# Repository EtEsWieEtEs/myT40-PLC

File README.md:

# myT40-PLC  (SPS) based on Teensy 4.0 (Version-5)
Hardware for PLC based on Teensy 4.0, covering all my needs. I have to replace my 30 years old PS4-141-MM1 from "Klöcker Moeller", reusing the original case of this model PS4-141-MM1.

Picture: Prototype V3

Motivation for a “Mighty 40”
----------------------------
Since the late 1990s, I have been working with four used PS4-141s, one PS4-341, both controllers from Klöckner Moeller, and about two dozen 24V AC surge relays (unfortunately not DC), commonly known as “Eltako,” I planned and developed my “smart home” in the late ’90s and installed it in my new house in 2002. 
The bus systems for building automation that were already on the market at the time were out of the question for me due to licensing issues and costs. 
These control units are networked and seamlessly integrated into my sub-distribution panels—commonly known as “fuse boxes”—on a circuit breaker (C) rail installed at the rear, just like standard circuit breakers. Circuit protection, power, and control are clearly separated in accordance with VDE standards.

Using serial communication, the master controller can be configured during operation using a user-friendly VB program (timer functions, lighting, roller shutters, light level detection, assignment of switches to power outlets such as wall sockets or ceiling outlets for lamps, etc.).

Since these controllers or similar devices are no longer manufactured in this format, the first failures occurred after nearly 30 years of trouble-free operation, and no other manufacturer offers affordable controllers with galvanic isolation(!) in this format anymore, I decided to strip down the PS4-141 housings and develop a new circuit that handles the most important functions and fits into these very housings I have on hand, hereinafter referred to as the “original housing.”

The result is "myT40-PLC", a combination of extention slot of PS4-341 in the housing of an P4S-141.

It is not intended to create a replica of the original, nor is that the goal. Externally, the case has been noticeably modified and fitted with different connectors: the “myT40-PLC”.

Since the circuit itself might also be of interest to others, I designed the main board in two versions for J3: one with an FFC connector, the “FFC” version, for my personal replacement in the original case, and a standard version with a pin header, the “PFS” version, to inspire replicas in any case. The latter is presented here.

This pin header connector "PFS" version offers a 2x DAC option and a 2x ADC option, while allowing the use of all 32 digital I/O channels and providing Sub-D connectors for bus systems in a separate housing. This distinguishes it from the FFC version, which cannot optionally provide all outputs when the DAC and ADC are installed and connected.

A parallel project, myT41-Controller, focuses on a controller unit that provides a graphical interface, Ethernet, CAN and RS485 buses, as well as a serial OTA interface, and allows the myT40 PLC to be controlled, logged, and configured.
With appropriate programming, the myT41C controller can also be used as a protocol converter or logger on the interfaces for entirely different projects.

The software will be documented separately at a later date.
This document describes only the hardware-related port definitions that result from the circuit and are essential for programming.

Attended documents describe the "Final Version V5" as "V3.3 M44", based on experience of 4 prototypes build up in the past 5 years.

The current Version is the final one waiting to be build-up: V5.
I made a lot of changes and enhancements and transfered these features as well to the myT41-Controller.

myT40-PLC      Requirements for my new PLC
------------------------------------------
Even though the new circuit cannot meet all the requirements of the original, I still have a clear idea of what it will be capable of.
The new controller should

1. be installed in my existing original enclosures or any other enclosures,
2. be networked so it can communicate with other devices,
3. ensure isolated potentials for inputs, load circuits, bus systems, ADC/DAC, and controllers; therefore, commercially available Arduino- or Raspberry Pi-based PLCs are out of the question,
4. provide 16 digital inputs and 16 digital outputs as needed, with isolated potentials,
5. support interrupts for input bytes,
6. Provide 4 analog-to-digital converter inputs if required, two of these are fed via built-in setpoint potentiometers,
7. Provide 2 digital-to-analog converter outputs if required,
8. Process analog signals from 0..10V, ADC and DAC, with their own reference potential,
9. Support up to two CAN buses, galvanically isolated, optionally GND, PE shield via capacitor,
10. Provide an RS485 interface for 16 clients, galvanically isolated, bus termination with low-drop diodes or optionally classically with switchable terminating resistor 720/120/720 ,
11. RS485 connection corresponds to the original (V5); the DIN sockets combine CAN1/2 and RS485,
12. be based on a modern, fast processor with sufficient RAM,
13. be supported by an EEPROM/Flash memory,
14. have ICs mounted on sockets wherever possible,
15. support a mode selector switch with 3 modes, including a setting for a cold start via RESET,
16. be able to use the existing RESET button,
17. be able to trigger a RESET via software, including a choice between cold or warm start,
18. ensure local communication via SPI for the interface and function modules,
19. be energy-efficient and operate at 3.3V,
20. be programmed in C or C++,
21. allow communication with a PC or a control unit via CAN, RS485, Ethernet,
22. enable flexible programming,
23. feature a pluggable, wired 3.6V backup lithium battery with its own ADC monitoring,
24. Respond to the 24V AC “Eltako” devices present in the building’s electrical system with 5ms DC pulses (!),
25. Monitor the supply voltages of the CPU and the direct interfaces and, if necessary, perform a warm start or cold start with a reset,     
26. Control the onboard hardware watchdog and/or software watchdog in combination with the operating mode switch, or allow them to function independently.
27. Does not support flexible docking of various original expansion modules; however, a suitable connection panel for SPI and digital I/O is available, though it is incompatible with original expansion modules. Instead, equip the existing 16-channel digital output unit with a new “header board” to make	it usable.
28. No online programming or programming via network, although this might actually be possible.
29. No PWM support on the outputs or counter features on the inputs.
30. External hardware watchdog with adjustable times, including a definable delay on RESET and restart (V5),
31. Buttons for Teensy 4.0 boot/program and on/off (V5),
32. OTA option (V5).
33. F-RAM SPI Option based on SOIC-8

Current developement
---------------------

Picture: Prototype V4 below, original defective pcb at top

Now that the Prototype 4 (V4) is working successfully with a 4-layer PCB, I have added an external watchdog and a delay into Version 5.

V5 offers optionally the use of OTA via one of the two serial interfaces instead of a second CAN bus.

Furthermore I think F-RAM is a good alternative for often changed written data to be stored permantly. So V5 provides a place for SOIC-8 alterntive to EEPROM in DIL-8.

However, Version 5 has not yet been built or tested. That is planned for the coming months.

There are some things to do like translation of documentation into English or Spanish, perhaps in next winter.
The current documentation is in German. 
So please be pacient, feel free and be inspired.

Licence
---------------------
This work is licensed under the Creatjve Commons Atuributjon-NonCommercial-ShareAlike 4.0 Internatjonal
License. To view a copy of this license, visit htup://creatjvecommons.org/licenses/by-nc-sa/4.0/ or send a
letuer to Creatjve Commons, PO Box 1866, Mountain View, CA 94042, USA.
This license lets others remix, adapt, and build upon your work non-commercially, as long as they credit you
and license their new creatjons under the identjcal terms.
htup://creatjvecommons.org/licenses/by-nc-sa/4.0/

  Title    myT40-PLC Documentation

  Author   Clemens Niesen, Germany, 2026

  Source   These documents

  Licence  CC-BY-NC-SA

DISCLAIMER
----------

I explicitly state that I make no representations or warranties regarding non-infringement or the absence of other defects with respect to the CC-licensed work.This means that users use the work at their own risk.

Furthermore, I point out that this project and the content of this documentation, as well as associated files, is purely a recreational project and should be understood as a case study for the reader. 

This project, these circuits are not tested or approved by official bodies. Errors can not be excluded despite all care. Whoever reproduces this project does so at his own risk and responsibility. I do not take any responsibility for damages to persons and devices, material, buildings, animals, etc..

Rebuilding is reserved exclusively for experienced people who know exactly what they are doing.  What third-party use of the control with third does and does not, lies apart from the craftsmanship of the construction also with the software, which is also beyond my responsibility. I give no guarantee and take no responsibility for the content of references, links and quotes.

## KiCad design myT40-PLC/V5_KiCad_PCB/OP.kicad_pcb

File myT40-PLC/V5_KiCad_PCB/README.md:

KiCad 9.0.7

myT40-PLC Rev3.3 M44 V5 PFS

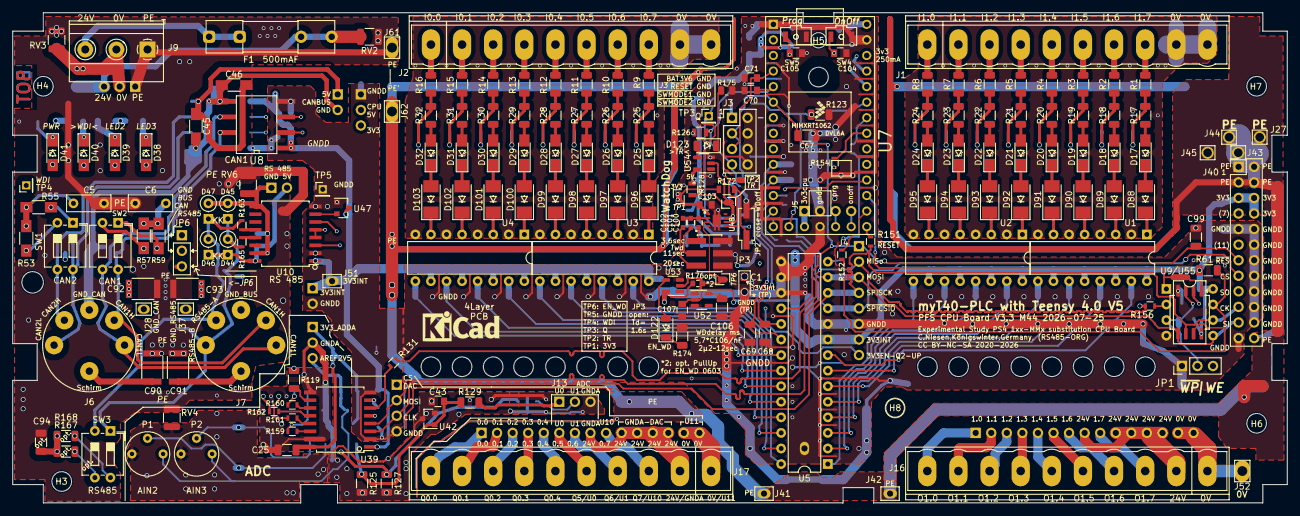
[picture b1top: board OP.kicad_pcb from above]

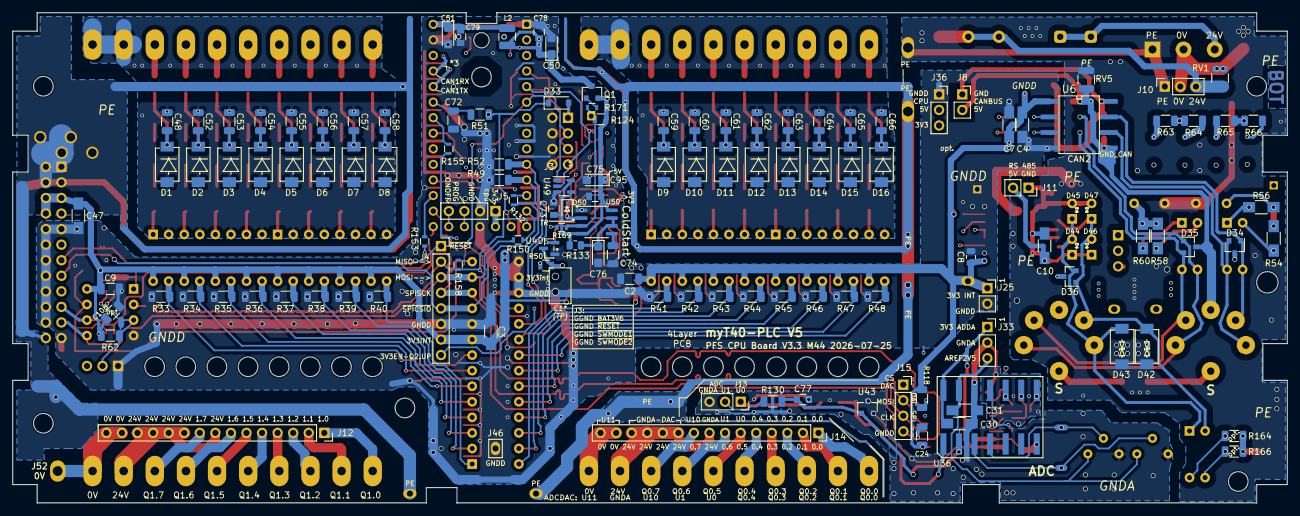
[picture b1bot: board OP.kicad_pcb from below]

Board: 4 copper layers, 208.0 x 80.0 mm, 341 parts (127 on the bottom side), 234 nets.

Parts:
A2: KiCad-Symbol; KiCad-Logo_5mm_SilkScreen
C1: Siehe Text; CP_EIA-3216-18_Kemet-A
C2, C9, C24, C25, C48, C52, C53, C54, C55, C56, C57, C58, C59, C60, C61, C62, C63, C64, C65, C66, C67, C68, C69, C72, C99, C108: 100n; C_1206_3216Metric
C3, C4, C7, C10, C30, C31, C47: 100n; C_1206_HandSoldering
C5, C6: 4n7; C_Rect_L7.0mm_W2.5mm_P5.00mm
C8: 100n; C_0805_2012Metric
C43, C77: 100p; C_0805
C45, C46: 100n 100V; C_1206_HandSoldering
C50, C51: 4µ7 16V; CP_EIA-3216-18_Kemet-A
C70, C71, C73, C75, C103, C104, C105, C107: 100n; C_0805
C74: 10n; C_1206_3216Metric
C76, C95: 10µ 10V; CP_EIA-3216-18_Kemet-A
C78, C79: 2,2pF; C_0805
C90, C91, C92, C93: 220n 250V; C_1812
C94: 220p 50V; C_1206_3216Metric
C100: 47n; C_0603
C101: 150n; C_0603
C102: 270n; C_0603
C106: 2µ2; C_1206_3216Metric
D1, D2, D3, D4, D5, D6, D7, D8, D9, D10, D11, D12, D13, D14, D15, D16: P6SMB 5,0CA SMD; DO-214AA_man
D17, D18, D19, D20, D21, D22, D23, D24, D25, D26, D27, D28, D29, D30, D31, D32, D38, D39, D40, D41: APTD3216; LED_1206_HandSoldering
D33: 1N4448W7F DII; D_SOD-123
D34, D35, D36: SZNUP2105LT1G; SOT-23
D42, D43: P6SMB 5,0CA; DO-214AA_man
D44, D45, D46, D47: BAT 46; D_DO-35_SOD27_P2.54mm_Vertical_KathodeUp
D50: RB751V40T1G; D_SOD-323
D88, D89, D90, D91, D92, D93, D94, D95, D96, D97, D98, D99, D100, D101, D102, D103: 1N4448W7F DII; Diode_DO213AB-MELF_SOD123
D122, D123: APTD3216; LED_1206_3216_big-gap
F1: 500mA F; Fuseholder_Clip-5x20mm_Littelfuse_111_Inline_P20.00x5.00mm_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
H1: MH2,5; Hole_2,5mm
H2: MH3,5; Hole_3,5mm
H3, H4, H5, H6, H7, H8: MountingHole; MountingHole_3.2mm_M3
H9, H10, H11, H12, H13, H14, H15, H16, H17, H18, H19, H20, H21, H22, H23, H24: LED3.2mm; Hole_3.2mm
J1, J2, J16, J17: MSTBVA-2.5-10-5.08; TerminalBlock_Phoenix_MSTBVA-2.5-10-5.08_1x10_P5.08mm_Horiz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
J3: 02x04; PinHeader_2x04_P2.54mm_Vertical
J4: 01x08_fem; PinSocket_1x08_P2.54mm_Vertical
J5, J15: 01x04_fem; PinSocket_1x04_P2.54mm_Vertical
J6, J7: DIN-5; DIN-5-180
J8, J11, J25: 01x02_fem; PinSocket_1x02_P2.54mm_Vertical
J9: Ub 0V PE; TerminalBlock_Phoenix_MKDS-1,5-3-5.08_1x03_P5.08mm_Horizont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
J10, J13, J33, J36: 01x03_fem; PinSocket_1x03_P2.54mm_Vertical
J12, J14: 01x15_fem; PinSocket_1x15_P2.54mm_Vertical
J27, J44, J45: Lötauge; Lötauge-Junction-2x2-1.4
J28: GND_CAN; Lötauge-Junction-2x1.5
J37: Lötauge; Lötauge-Junction-2x1.5
J40: Extention; PinHeader_2x12_P2.54mm_Vertical
J41, J42, J46, J51: Lötauge; Lötauge-Junction
J43: Flachstecker; Lötauge-Junction-2x2-1.4
J52: Lötauge; Lötauge-Junction-3.5x2.5-1.6
J61, J62: Lötauge; Lötauge-Junction-3.5x2.0-1.6
JP1: WP_; PinHeader_1x03_P2.54mm_Vertical
JP2: Jumper_NC_Small; PinHeader_2x01_P2.54mm_Vertical_SMD
JP3: jumper field; SAMTEC_TMMH-103-01-G-DV-A_PinHeader-02x03-SMD
JP6: GND-DEF.J7; PinHeader_1x03_P2.54mm_Vertical
L2: 47µH; L_1210_3225Metric
P1, P2: 1,0K lin; Trimmer_Vishay_T7YA
Q1: IRLML 2244; SOT-23
R1, R2, R3, R4, R5, R6, R7, R8, R9, R10, R11, R12, R13, R14, R15, R16: 6k8 500mW; R_1206_3216Metric
R17, R18, R19, R20, R21, R22, R23, R24, R25, R26, R27, R28, R29, R30, R31, R32: 1k1; R_1206_3216Metric
R33, R34, R35, R36, R37, R38, R39, R40, R41, R42, R43, R44, R45, R46, R47, R48: 3k3; R_1206_3216Metric
R49, R52, R61, R62, R118, R119: 10k; R_1206_3216Metric
R50, R126: 220; R_0805
R51, R123: 680k; R_1206_3216Metric
R53, R54, R55, R56, R57, R58, R59, R60: 120; R_1206_HandSoldering
R63, R64, R65, R66, R174: 1650; R_1206_3216Metric
R124: 10k; R_0805
R125, R127: 30k 0,1%; R_1206_3216Metric
R128: 47k; R_0805
R129, R130: 90k 0,1%; R_1206_3216Metric
R131, R132, R150, R151, R152, R153, R154, R155, R156, R158, R159, R160, R161, R162: 51; R_0603
R133: 220k; R_0805_2012Metric
R163, R165, R169, R171: 10; R_0603
R164, R166, R167, R168: 120; R_1206_3216Metric
R172: 1k; R_1206_vertical
R175: 3k3; R_0805_2012Metric
R176: 10k; R_0603_1608Metric
RV1, RV2, RV3: 31VDC; R_1210_3225Metric
RV4, RV5, RV6: 46VAC; R_1210_3225Metric
SW1, SW2: SW_DIP_x02; SW_DIP_SPSTx02_Slide_6.7x6.64mm_W7.62mm_P2.54mm_LowProfile
SW3: GDS0204; SW_DIP_SPSTx02_Slide_6.7x6.64mm_W7.62mm_P2.54mm_LowProfile
SW4: OnOff; switch-tactil_OMRON_B3U-3000P
SW5: Prog; switch-tactil_OMRON_B3U-3000P
TP1: 3V3; TestPoint_SMD
TP2: TR; TestPoint_SMD
TP3: Q; PinHeader_1x01_P2.00mm_Vertical
TP4: WDI; PinHeader_1x01_P2.00mm_Vertical
TP5: GNDD; PinHeader_1x01_P2.00mm_Vertical
TP6: EN_WD; TestPoint_SMD
U1, U2, U3, U4: LTV-844; DIP-16_W7.62mm_cut
U5: MCP23S17; DIP-28_W7.62mm
U6, U8: ISO1050; SOP-8
U7: Teensy4.0; Teensy40wo34_0.9
U9: 25LC512; DIP-8_W7.62mm
U10: ADM2483xRW; SOIC-16W_7.5x10.3mm_Pitch1.27mm_handsoldered
U36: MCP3204; DIL-14-SMD
U39: ADuM1401xRW; SOIC-16W_7.5x10.3mm_Pitch1.27mm_handsoldered
U40: ADM-803S; SOT-23
U42, U43: LM4040 AIM3-2.5; SOT-23
U47: ADM-809Z; SOT-23
U48: TPS3431; VSON-8_EP_2.8x2.8_Pitch0.65mm
U49: SN74LV1T32; SOT-23-5
U50: NE555DRG4; SOIC-8_3.9x4.9mm_P1.27mm
U52: S-80929CNMC; SOT-23-5
U53, U54: BD7LS04G-C; SOT-23-5
U55: FM25V10; SOIC-8_5.3x6.2mm_P1.27mm

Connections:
3V3: C103.1, J36.3, R50.1, R126.2, R172.1, R176.1, TP1.1, U40.3 (VCC), U48.1 (VDD), U53.5 (3V3)
5V_CPU: C73.2, C75.2, C95.1, J36.2, Q1.2 (S), R124.2, R128.2, R133.2, U49.5 (5V_CPU), U50.4 (R), U50.8 (VCC), U54.5 (5V_CPU)
/3V3EN_Q2_UP: J4.8, R169.2
/3V3_ADDA: C25.2, C30.2, J33.1, R119.2, U36.14 (Vdd), U39.16 (VDD2)
/3V3_CPU: J5.1, U7.16 (3V3)
/3V3_INT: C1.1, C2.1, C3.2, C4.1, C7.2, C8.1, C9.2, C24.2, C47.2, C107.1, C108.2, D41.2 (A), J4.7, J25.1, J40.5, J40.6, J40.8, J51.1, R61.1, R62.1, R118.2, U1.10, U1.12, U1.14, U1.16, U2.10, U2.12, U2.14, U2.16, U3.10, U3.12, U3.14, U3.16, U4.10, U4.12, U4.14, U4.16, U5.9 (VDD), U6.1 (VCC1), U8.1 (VCC1), U9.8 (VCC), U10.1 (VDD1), U39.1 (VDD1), U47.3 (VCC), U52.2 (VDD), U55.8 (VCC)
/5V_CPU_final: C51.1, C79.1, L2.2, U7.33 (VIN)
/AIN0: J13.1, R129.1
/AIN1: J13.2, R130.1
/AREF_2V5: C31.2, J33.3, P1.3, P2.3, U36.13 (Vref)
/BAT3V6: D33.2 (A), J3.1
/BAT_CHECK: C72.1, R51.2, U7.28 (21_A7_RX5_BCLK1)
/CAN1H: D35.2 (A2), J6.5, J7.5, SW2.4, U8.7 (CANH)
/CAN1L: D35.1 (A1), J6.3, J7.3, SW2.3, U8.6 (CANL)
/CAN1RX: U7.30 (23_A9_CRX1_MCLK1), U8.2 (RXD)
/CAN1TX: U7.29 (22_A8_CTX1), U8.3 (TXD)
/CAN2H: D34.1 (A1), J6.4, SW1.3, U6.7 (CANH)
/CAN2L: D34.2 (A2), J6.1, SW1.4, U6.6 (CANL)
/CAN2RX: U6.2 (RXD), U7.2 (0_RX1_CRX2)
/CAN2TX: U6.3 (TXD), U7.3 (1_TX1_CTX2)
/CH0: C43.1, R125.1, R129.2, U36.1 (CH0), U42.1 (K)
/CH1: C77.1, R127.1, R130.2, U36.2 (CH1), U43.1 (K)
/CH2: P1.2, U36.3 (CH2)
/CH3: P2.2, U36.4 (CH3)
/CLK: R159.2, U36.11 (CLK)
/Din: R161.2, U36.9 (Din)
/Dout: R160.2, U36.10 (Dout)
/EN_WD: R176.2, TP6.1, U48.3 (EN), U52.1 (OUT), U53.2
/GND_CAN_BUS: C45.2, C46.1, C92.1, D34.3 (common), D35.3 (common), J6.2, J8.2, J28.1, JP6.1 (A), RV5.2, U6.5 (GND2), U8.5 (GND2)
/GND_RS485_BUS: C10.1, C93.2, D36.3 (common), D45.2 (A), D47.2 (A), J11.1, J37.1, JP6.3 (B), RV6.2, U10.9 (GND2), U10.15 (GND2)
/INTA: C69.1, R52.1, U5.20 (INTA), U7.10 (8_TX2_IN1)
/INTB: C68.1, R49.1, U5.19 (INTB), U7.11 (9_OUT1C)
/I_GPA0: R48.2, U4.9, U5.21 (GPA0)
/I_GPA1: R47.2, U4.11, U5.22 (GPA1)
/I_GPA2: R46.2, U4.13, U5.23 (GPA2)
/I_GPA3: R45.2, U4.15, U5.24 (GPA3)
/I_GPA4: R44.2, U3.9, U5.25 (GPA4)
/I_GPA5: R43.2, U3.11, U5.26 (GPA5)
/I_GPA6: R42.2, U3.13, U5.27 (GPA6)
/I_GPA7: R41.2, U3.15, U5.28 (GPA7)
/I_GPB0: R40.2, U2.9, U5.1 (GPB0)
/I_GPB1: R39.2, U2.11, U5.2 (GPB1)
/I_GPB2: R38.2, U2.13, U5.3 (GPB2)
/I_GPB3: R37.2, U2.15, U5.4 (GPB3)
/I_GPB4: R36.2, U1.9, U5.5 (GPB4)
/I_GPB5: R35.2, U1.11, U5.6 (GPB5)
/I_GPB6: R34.2, U1.13, U5.7 (GPB6)
/I_GPB7: R33.2, U1.15, U5.8 (GPB7)
/LED1: D40.2 (A), TP4.1, U7.7 (5_IN2), U48.6 (WDI)
/LED2: D39.2 (A), U7.8 (6_OUT1D)
/LED3: D38.2 (A), U7.9 (7_RX2_OUT1A)
/MISO: J4.2, J40.17, R131.1, R156.2, R158.2, U7.14 (12_MISO_MQSL)
/MISO_0: R156.1, U9.2 (MISO), U55.2 (MISO)
/MOSI: J4.3, J15.2, J40.21, R150.1, U5.13 (SI), U9.5 (MOSI), U39.4 (VIB), U55.5 (MOSI)
/ONOFF: C104.1, J5.4, SW4.2, U7.19 (ON_OFF)
/PROGRAM: C105.1, J5.3, SW5.2, U7.18 (PROGRAM)
/Q: R124.1, R169.1, R171.1, TP3.1, U50.3 (Q)
/RS485_A: D36.1 (A1), D42.2 (A2), D46.2 (A), D47.1 (K), J7.4, R163.1, SW3.2
/RS485_B: D36.2 (A2), D43.2 (A2), D44.2 (A), D45.1 (K), J7.1, R165.1, SW3.1
/SPISCK: J4.4, J15.3, J40.19, R151.1, U5.12 (SCK), U9.6 (SCK), U39.3 (VIA), U55.6 (SCK)
/TR-U50: D50.2 (A), R128.1, TP2.1, U40.2 (~RESET), U48.7 (~WDO), U50.2 (TR), U54.2
/U0V: J9.2, J10.2, RV1.1, RV3.2
/U24V: F1.2, J10.3, RV1.2, RV2.2
/UART_RX: U7.23 (16_A2_RX4_SCL1), U10.3 (RxD)
/UART_TX: U7.24 (17_A3_TX4_SDA1), U10.6 (TxD)
/Ub_5V_RS485_BUS: C10.2, D44.1 (K), D46.1 (K), J11.2, U10.16 (VDD2)
/Ub_CAN_BUS: C45.1, C46.2, J8.1, U6.8 (VCC2), U8.8 (VCC2)
/VBAT: D33.1 (K), R51.1, R123.1, U7.15 (VBAT)
/~CS: R162.2, U36.8 (~CS/SHDN)
/~EE_HOLD: R61.2, R152.1, U9.7 (~HOLD), U55.7 (~HOLD)
/~RESET: C67.1, C99.2, J3.3, J4.1, J40.13, R50.2, U5.18 (~RESET), U7.6 (4_BCLK2), U49.1
/~SPICS_ADC: R154.1, U39.5 (VIC)
/~SPICS_DAC: J15.1, R155.1
/~SPICS_EE: R153.1, U9.1 (~CS), U55.1 (~CS)
/~SPICS_IO: J4.5, J40.15, R132.1, U5.11 (~CS)
/~SW_MODE_1: C71.1, J3.5, U7.4 (2_OUT2)
/~SW_MODE_2: C70.1, J3.7, R126.1, U7.5 (3_LRCLK2), U49.2
/~UART_RE: U7.25 (18_A4_SDA0), U10.4 (~RE), U10.5 (DE)
/~WP: JP1.2 (C), R62.2, U9.3 (~WP), U55.3 (~WP)
GNDA: C25.1, C30.1, C31.1, C43.2, C77.2, J13.3, J33.2, P1.1, P2.1, R125.2, R127.2, RV4.2, U36.7 (DGND), U36.12 (AGND), U39.9 (GND2), U39.15 (GND2), U42.2 (A), U42.3 (3(A)), U43.2 (A), U43.3 (3(A))
GNDD: C1.2, C2.2, C3.1, C4.2, C7.1, C8.2, C9.1, C24.1, C47.1, C50.2, C51.2, C67.2, C68.2, C69.2, C70.2, C71.2, C72.2, C73.1, C74.1, C75.1, C76.2, C78.2, C79.2, C95.2, C99.1, C103.2, C104.2, C105.2, C106.2, C107.2, C108.1, J3.2, J3.4, J3.6, J3.8, J4.6, J5.2, J15.4, J25.2, J36.1, J40.9, J40.10, J40.12, J40.14, J40.16, J40.18, J40.20, J40.22, J40.23, J46.1, JP1.1 (A), JP2.2, JP3.02, JP3.04, JP3.06, R33.1, R34.1, R35.1, R36.1, R37.1, R38.1, R39.1, R40.1, R41.1, R42.1, R43.1, R44.1, R45.1, R46.1, R47.1, R48.1, R49.2, R52.2, R63.1, R64.1, R65.1, R66.1, R123.2, R174.1, R175.1, SW4.1, SW5.1, TP5.1, U5.10 (VSS), U5.15 (A0), U5.16 (A1), U5.17 (A2), U6.4 (GND1), U7.1 (GND), U7.17 (GND), U7.32 (GND), U8.4 (GND1), U9.4 (GND), U10.2 (GND1), U10.8 (GND1), U39.2 (GND1), U39.8 (GND1), U40.1 (GND), U47.1 (GND), U48.4 (GND), U48.9 (Pad), U49.3 (GNDD), U50.1 (GND), U52.3 (VSS), U53.3 (GNDD), U54.3 (GNDD), U55.4 (GND)
unnamed: C5.2, R53.1, R54.1, R55.1, R56.1
unnamed: C6.2, R57.1, R58.1, R59.1, R60.1
unnamed: C90.2, J6.S
unnamed: C91.2, J7.S
unnamed: C94.2, R164.2, R166.2, R167.2, R168.2
unnamed: C100.2, JP3.01
unnamed: C101.1, JP3.03
unnamed: C102.1, JP3.05
unnamed: C48.1, C52.1, C53.1, C54.1, C55.1, C56.1, C57.1, C58.1, D1.1 (A1), D2.1 (A1), D3.1 (A1), D4.1 (A1), D5.1 (A1), D6.1 (A1), D7.1 (A1), D8.1 (A1), J1.9, J1.10, U1.2, U1.4, U1.6, U1.8, U2.2, U2.4, U2.6, U2.8
unnamed: C48.2, D1.2 (A2), R1.1, R17.2
unnamed: C52.2, D2.2 (A2), R2.1, R18.2
unnamed: C53.2, D3.2 (A2), R3.1, R19.2
unnamed: C54.2, D4.2 (A2), R4.1, R20.2
unnamed: C55.2, D5.2 (A2), R5.1, R21.2
unnamed: C56.2, D6.2 (A2), R6.1, R22.2
unnamed: C57.2, D7.2 (A2), R7.1, R23.2
unnamed: C58.2, D8.2 (A2), R8.1, R24.2
unnamed: C59.2, D9.2 (A2), R9.1, R25.2
unnamed: C59.1, C60.1, C61.1, C62.1, C63.1, C64.1, C65.1, C66.1, D9.1 (A1), D10.1 (A1), D11.1 (A1), D12.1 (A1), D13.1 (A1), D14.1 (A1), D15.1 (A1), D16.1 (A1), J2.9, J2.10, U3.2, U3.4, U3.6, U3.8, U4.2, U4.4, U4.6, U4.8
unnamed: C60.2, D10.2 (A2), R10.1, R26.2
unnamed: C61.2, D11.2 (A2), R11.1, R27.2
unnamed: C62.2, D12.2 (A2), R12.1, R28.2
unnamed: C63.2, D13.2 (A2), R13.1, R29.2
unnamed: C64.2, D14.2 (A2), R14.1, R30.2
unnamed: C65.2, D15.2 (A2), R15.1, R31.2
unnamed: C66.2, D16.2 (A2), R16.1, R32.2
unnamed: D17.2 (A), R17.1
unnamed: D17.1 (K), D88.2 (A)
unnamed: D18.2 (A), R18.1
unnamed: D18.1 (K), D89.2 (A)
unnamed: D19.2 (A), R19.1
unnamed: D19.1 (K), D90.2 (A)
unnamed: D20.2 (A), R20.1
unnamed: D20.1 (K), D91.2 (A)
unnamed: D21.2 (A), R21.1
unnamed: D21.1 (K), D92.2 (A)
unnamed: D22.2 (A), R22.1
unnamed: D22.1 (K), D93.2 (A)
unnamed: D23.2 (A), R23.1
unnamed: D23.1 (K), D94.2 (A)
unnamed: D24.2 (A), R24.1
unnamed: D24.1 (K), D95.2 (A)
unnamed: D25.2 (A), R25.1
unnamed: D25.1 (K), D96.2 (A)
unnamed: D26.2 (A), R26.1
unnamed: D26.1 (K), D97.2 (A)
unnamed: D27.2 (A), R27.1
unnamed: D27.1 (K), D98.2 (A)
unnamed: D28.2 (A), R28.1
unnamed: D28.1 (K), D99.2 (A)
unnamed: D29.2 (A), R29.1
unnamed: D30.2 (A), R30.1
unnamed: D31.2 (A), R31.1
unnamed: D32.2 (A), R32.1
unnamed: D38.1 (K), R63.2
unnamed: D39.1 (K), R64.2
unnamed: D40.1 (K), R65.2
unnamed: D41.1 (K), R66.2
unnamed: D50.1 (K), U49.4
unnamed: D88.1 (K), U1.1
unnamed: D89.1 (K), U1.3
unnamed: D90.1 (K), U1.5
unnamed: D91.1 (K), U1.7
unnamed: D92.1 (K), U2.1
unnamed: D93.1 (K), U2.3
unnamed: D94.1 (K), U2.5
unnamed: D95.1 (K), U2.7
unnamed: D96.1 (K), U3.1
unnamed: D97.1 (K), U3.3
unnamed: D98.1 (K), U3.5
unnamed: D99.1 (K), U3.7
unnamed: D29.1 (K), D100.2 (A)
unnamed: D100.1 (K), U4.1
unnamed: D30.1 (K), D101.2 (A)
unnamed: D101.1 (K), U4.3
unnamed: D31.1 (K), D102.2 (A)
unnamed: D102.1 (K), U4.5
unnamed: D32.1 (K), D103.2 (A)
unnamed: D103.1 (K), U4.7
unnamed: D122.2 (A), U53.4
unnamed: D122.1 (K), R174.2
unnamed: D123.2 (A), U54.4
unnamed: D123.1 (K), R175.2
unnamed: J1.1, R8.2
unnamed: J1.2, R7.2
unnamed: J1.3, R6.2
unnamed: J1.4, R5.2
unnamed: J1.5, R4.2
unnamed: J1.6, R3.2
unnamed: J1.7, R2.2
unnamed: J1.8, R1.2
unnamed: J2.1, R16.2
unnamed: J2.2, R15.2
unnamed: J2.3, R14.2
unnamed: J2.4, R13.2
unnamed: J2.5, R12.2
unnamed: J2.6, R11.2
unnamed: J2.7, R10.2
unnamed: J2.8, R9.2
unnamed: F1.1, J9.3
unnamed: J12.1, J16.10
unnamed: J12.2, J16.9
unnamed: J12.3, J16.8
unnamed: J12.4, J16.7
unnamed: J12.5, J16.6
unnamed: J12.6, J16.5
unnamed: J12.7, J16.4
unnamed: J12.9, J16.3
unnamed: J12.8, J12.10, J12.11, J12.12, J12.13, J16.2
unnamed: J12.14, J12.15, J16.1, J52.1
unnamed: J14.1, J17.10
unnamed: J14.2, J17.9
unnamed: J14.3, J17.8
unnamed: J14.4, J17.7
unnamed: J14.5, J17.6
unnamed: J14.6, J17.5
unnamed: J14.7, J17.4
unnamed: J14.9, J17.3
unnamed: J14.8, J14.10, J14.11, J14.12, J14.13, J17.2
unnamed: J14.14, J14.15, J17.1
unnamed: J7.2, JP6.2 (C)
unnamed: C50.1, C78.1, L2.1, Q1.3 (D)
unnamed: Q1.1 (G), R171.2
unnamed: R53.2, R54.2, SW1.2
unnamed: R55.2, R56.2, SW1.1
unnamed: R57.2, R58.2, SW2.2
unnamed: R59.2, R60.2, SW2.1
unnamed: R164.1, R168.1, SW3.4
unnamed: R166.1, R167.1, SW3.3
unnamed: R158.1, U5.14 (SO)
unnamed: R132.2, U7.12 (10_CS_MQSR)
unnamed: R150.2, U7.13 (11_MOSI_CTX1)
unnamed: R151.2, U7.20 (13_SCK_CRX1_LED)
unnamed: R152.2, U7.21 (14_A0_TX3_SPDIF_OUT)
unnamed: R153.2, U7.22 (15_A1_RX3_SPDIF_IN)
unnamed: R154.2, U7.26 (19_A5_SCL0)
unnamed: R155.2, U7.27 (20_A6_TX5_LRCLK1)
unnamed: R163.2, U10.12 (A)
unnamed: R165.2, U10.13 (B)
unnamed: U10.7 (PV), U47.2 (~RESET)
unnamed: R118.1, U39.7 (VE1)
unnamed: R119.1, U39.10 (VE2)
unnamed: R160.1, U39.11 (VID)
unnamed: R159.1, U39.14 (VOA)
unnamed: R161.1, U39.13 (VOB)
unnamed: R162.1, U39.12 (VOC)
unnamed: R131.2, U39.6 (VOD)
unnamed: C100.1, C101.2, C102.2, U48.2 (CWD)
unnamed: JP2.1, R172.2, U48.5 (SET1)
unnamed: C74.2, U50.5 (CV)
unnamed: C76.1, R133.1, U50.6 (THR), U50.7 (DIS)
unnamed: C106.1, U52.5 (CD)
PE: C5.1, C6.1, C90.1, C91.1, C92.2, C93.1, C94.1, D42.1 (A1), D43.1 (A1), J9.1, J10.1, J27.1, J40.1, J40.2, J40.3, J40.4, J40.24, J41.1, J42.1, J43.1, J44.1, J45.1, J61.1, J62.1, RV2.1, RV3.1, RV4.1, RV5.1, RV6.1

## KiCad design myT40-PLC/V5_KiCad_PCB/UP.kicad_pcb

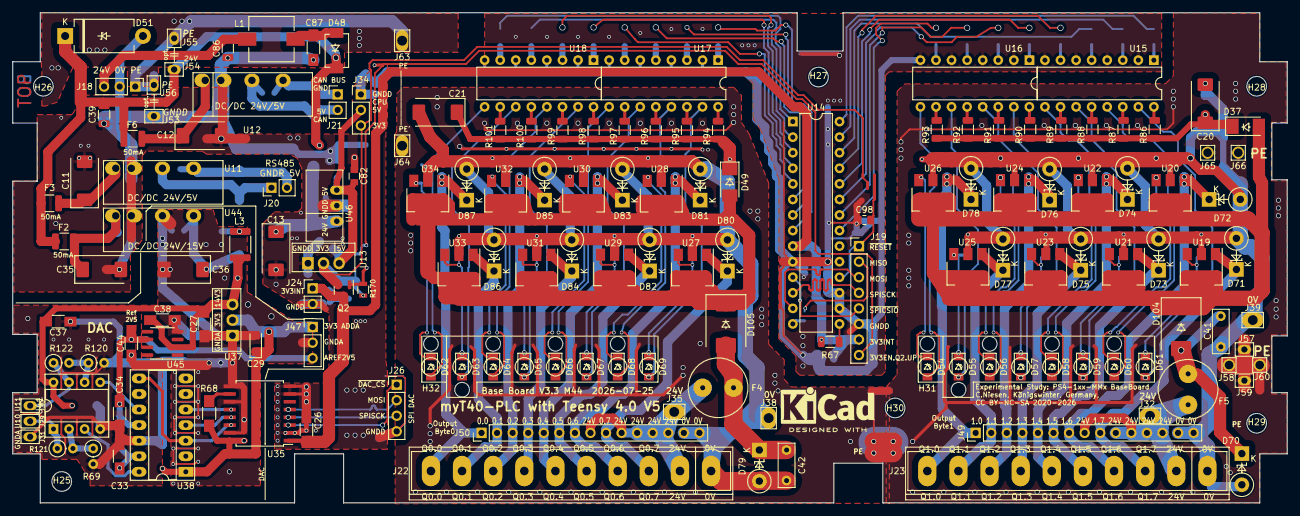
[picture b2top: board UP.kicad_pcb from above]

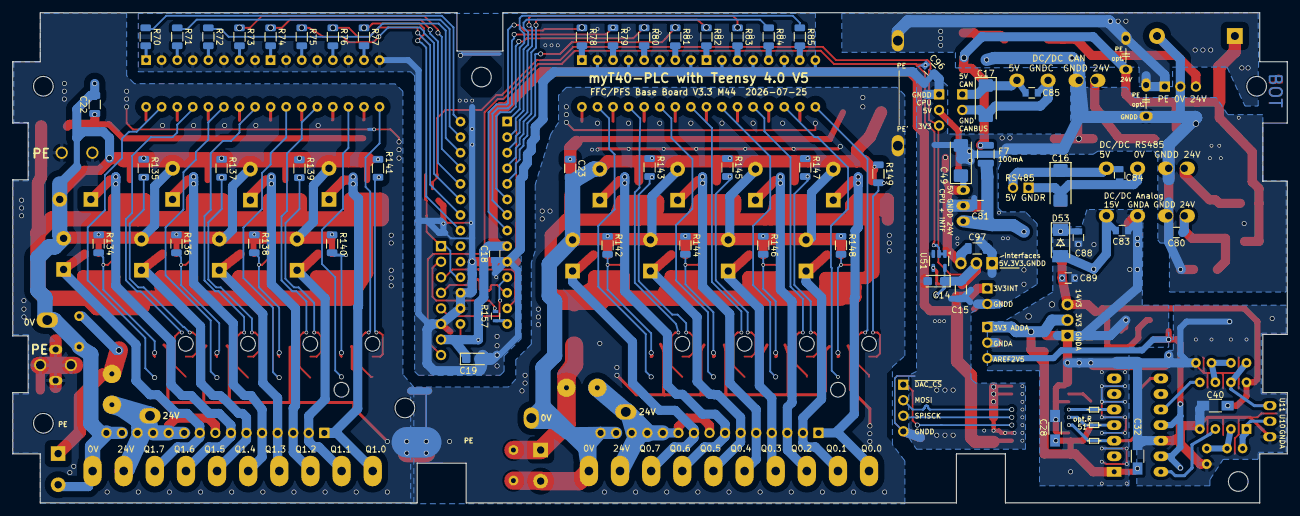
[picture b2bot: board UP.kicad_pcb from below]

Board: 2 copper layers, 208.0 x 80.0 mm, 221 parts (57 on the bottom side), 148 nets.

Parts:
A1: KiCad Symbol; KiCad-Logo2_6mm_SilkScreen
C11, C12, C13, C35: 10µ 50V; CP_EIA-7343-31_Kemet-D
C14: 22µ 6V3; CP_EIA-3216-18_Kemet-A
C15, C39: 100n 50V; C_1206_3216Metric
C16, C17, C49: 22µ 10V; CP_EIA-6032-28_Kemet-C
C18, C96: 100n; C_0805
C19: 2µ2 16V; CP_EIA-3216-18_Kemet-A
C20, C21: 2µ2 50V; CP_EIA-7343-31_Kemet-D
C22, C23, C86, C97: 100n; C_1206_3216Metric
C26, C27, C28, C32, C33, C34, C37, C38, C40, C44, C87: 100n; C_1206_HandSoldering
C29: 10µ 10V; CP_EIA-3216-18_Kemet-A
C36: 22µ 25V; CP_EIA-7343-31_Kemet-D
C41, C42: 100n; C_Rect_L7.0mm_W2.5mm_P5.00mm
C80, C81, C82, C83, C84, C85, C88, C89: 100n 50V; C_0805
C98: 100n; C_0805_2012Metric
D37, D49: 1N4448W7F DII; Diode_DO213AB-MELF_SOD123
D48: MBRS 1100 SMD; DO-214AA_Schottky_man
D51: 1.5KE27CA; D_DO-201_P12.70mm_Horizontal
D53: 1N4007 SMD; Diode_DO213AB-MELF_SOD123
D54, D55, D56, D57, D58, D59, D60, D61, D62, D63, D64, D65, D66, D67, D68, D69: KPTD-3216; D_1206_4.5
D70, D71, D72, D73, D74, D75, D76, D77, D78, D79, D80, D81, D82, D83, D84, D85, D86, D87: P6KE33CA; D_DO-15_P5.08mm_Vertical_KathodeUp
D104, D105: SK86; D_SMC
F2, F3, F6: 50mA; R_1210_3225Metric
F4, F5: 5,6AT; Sockel_Kleinst-F
F7: 100mA; R_1210_3225Metric
H25, H26, H27, H28, H29, H30: MountingHole; MountingHole_3.2mm_M3
H31, H32: LED-Licht-Leiter_8x3mm_P5.08; MEN-LED-Lichtleiter_8x3mm_P5.08_5v8
J18, J34, J47: 01x03_Male; PinHeader_1x03_P2.54mm_Vertical
J19: 01x08_Male; PinHeader_1x08_P2.54mm_Vertical
J20, J21, J24: 01x02_Male; PinHeader_1x02_P2.54mm_Vertical
J22, J23: opt. Connector; TerminalBlock_Phoenix_MSTBVA-2.5-10-5.08_1x10_P5.08mm_Horiz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
J26: 01x04_Male; PinHeader_1x04_P2.54mm_Vertical
J29: DAC 3pol J29-J31; Lötauge-Junction
J30, J31, J53, J54, J55, J56, J57, J59: Lötauge; Lötauge-Junction
J32, J35, J38, J39: Lötauge; Lötauge-Junction-3.5x2.5-1.6
J49, J50: 01x15 Male zu OP; PinHeader_1x15_P2.54mm_Vertical
J58, J60, J65: Lötauge; Lötauge-Junction-2x2-1.4
J63, J64: Lötauge; Lötauge-Junction-3.5x2.0-1.6
J66: Flachstecker; Lötauge-Junction-2x2-1.4
L1: PIS2812-271M-04; L_7.3x7.3_H3.5_handsoldered
L3: L-1812AF 330µ 100mA; L_1812_4532Metric
Q2: IRLML 2244; SOT-23
R67: 10k; R_1206_3216Metric
R68: 10k; R_1206_HandSoldering
R69, R120: 1k 0,1%; R_Axial_DIN0207_L6.3mm_D2.5mm_P2.54mm_Vertical
R70, R71, R72, R73, R74, R75, R76, R77, R78, R79, R80, R81, R82, R83, R84, R85: 1650; R_1206_3216Metric
R86, R87, R88, R89, R90, R91, R92, R93, R94, R95, R96, R97, R98, R99, R100, R101, R134, R135, R136, R137, R138, R139, R140, R141, R142, R143, R144, R145, R146, R147, R148, R149: 7k5; R_1206_3216Metric
R121, R122: 3k0 0,1%; R_Axial_DIN0207_L6.3mm_D2.5mm_P2.54mm_Vertical
R157: 51; R_0603
R170: 10k; R_0805
U11, U12: 2S7WA_2405_S3RP; SIP-7_2S7WA
U13, U37: LT1086 3.3; TO-220-3_Vertical
U14: MCP23S17; DIP-28_W7.62mm
U15, U16, U17, U18: LTV-844; DIP-16_W7.62mm_cut
U19, U20, U21, U22, U23, U24, U25, U26, U27, U28, U29, U30, U31, U32, U33, U34: BSP-452; SOT-223
U35: ADuM1401xRW; SOIC-16W_7.5x10.3mm_Pitch1.27mm_handsoldered
U38: MCP4922; DIP-14_W7.62mm_Socket_LongPads
U41: LT 1078; DIP-8_W7.62mm_Socket
U44: 2S7WB_2415S3RP; SIP-7_2S7WA
U45: ADR03ARZ; SOIC-8_3.9x4.9mm_P1.27mm
U46: LCN78_05-1.0; SIP-3-LC78
U51: SN74LV1T08; SOT-23-5

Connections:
3V3: C14.1, C15.1, J34.3, Q2.2 (S), R170.2, U13.2 (VO), U51.5 (3V3)
/3V3EN_Q2_UP: C96.1, J19.8, U51.1, U51.2
/3V3_ADDA: C28.2, C29.1, C32.2, J47.1, R68.1, U35.16 (VDD2), U37.2 (VO), U38.1 (VDD)
/3V3_INT: C18.2, C19.1, C26.2, J19.7, J24.1, Q2.3 (D), R67.1, U14.9 (VDD), U35.1 (VDD1)
/5V_CPU: C49.1, C82.1, C97.1, J34.2, U13.3 (VI), U46.3 (OUT)
/12V_ADDA: C27.2, C37.2, C38.2, C40.2, C89.1, L3.1, U37.3 (VI), U41.8 (V+), U45.2 (IN)
/24V: C39.1, D48.1 (K), D51.1 (A1), F2.2, F3.2, F6.2, F7.2, J54.1
/24V_F4: C42.1, D79.1 (A1), D105.2 (A), F4.2
/24V_F5: C41.1, D70.1 (A1), D104.2 (A), F5.2
/24V_OPT_1: C20.1, C22.1, D37.1 (K), R86.1, R87.1, R88.1, R89.1, R90.1, R91.1, R92.1, R93.1
/24V_OPT_2: C21.1, C23.1, D49.1 (K), R94.1, R95.1, R96.1, R97.1, R98.1, R99.1, R100.1, R101.1
/24V_Out_0: D49.2 (A), D105.1 (K), U27.4 (VCC), U28.4 (VCC), U29.4 (VCC), U30.4 (VCC), U31.4 (VCC), U32.4 (VCC), U33.4 (VCC), U34.4 (VCC)
/24V_Out_1: D37.2 (A), D104.1 (K), U19.4 (VCC), U20.4 (VCC), U21.4 (VCC), U22.4 (VCC), U23.4 (VCC), U24.4 (VCC), U25.4 (VCC), U26.4 (VCC)
/AREF_2V5: C33.2, C34.2, C44.2, J47.3, U38.11 (VrefB), U38.13 (VrefA), U45.6 (OUT)
/DAC_A: U38.14 (VoutA), U41.3 (+)
/DAC_B: U38.10 (VoutB), U41.5 (+)
/DAC_OUT_A: J29.1, R121.1, U41.1
/DAC_OUT_B: J30.1, R122.1, U41.7
/GNDPWR_Out_0: C21.2, C23.2, C42.2, D79.2 (A2), D80.2 (A2), D81.2 (A2), D82.2 (A2), D83.2 (A2), D84.2 (A2), D85.2 (A2), D86.2 (A2), D87.2 (A2), J22.1, J38.1, J50.14, J50.15, R142.1, R143.1, R144.1, R145.1, R146.1, R147.1, R148.1, R149.1, U27.2 (GND), U28.2 (GND), U29.2 (GND), U30.2 (GND), U31.2 (GND), U32.2 (GND), U33.2 (GND), U34.2 (GND)
/GNDPWR_Out_1: C20.2, C22.2, C41.2, D70.2 (A2), D71.2 (A2), D72.2 (A2), D73.2 (A2), D74.2 (A2), D75.2 (A2), D76.2 (A2), D77.2 (A2), D78.2 (A2), J23.1, J39.1, J49.14, J49.15, R134.1, R135.1, R136.1, R137.1, R138.1, R139.1, R140.1, R141.1, U19.2 (GND), U20.2 (GND), U21.2 (GND), U22.2 (GND), U23.2 (GND), U24.2 (GND), U25.2 (GND), U26.2 (GND)
/GND_CAN_BUS: C17.2, C85.2, J21.2, U12.4 (Out-)
/GND_RS485_BUS: C16.2, C84.2, J20.1, U11.4 (Out-)
/MISO: J19.2, R157.1
/MOSI: J19.3, J26.2, U14.13 (SI), U35.5 (VIC)
/O_GPA0: R77.1, U14.21 (GPA0)
/O_GPA1: R76.1, U14.22 (GPA1)
/O_GPA2: R75.1, U14.23 (GPA2)
/O_GPA3: R74.1, U14.24 (GPA3)
/O_GPA4: R73.1, U14.25 (GPA4)
/O_GPA5: R72.1, U14.26 (GPA5)
/O_GPA6: R71.1, U14.27 (GPA6)
/O_GPA7: R70.1, U14.28 (GPA7)
/O_GPB0: R85.1, U14.1 (GPB0)
/O_GPB1: R84.1, U14.2 (GPB1)
/O_GPB2: R83.1, U14.3 (GPB2)
/O_GPB3: R82.1, U14.4 (GPB3)
/O_GPB4: R81.1, U14.5 (GPB4)
/O_GPB5: R80.1, U14.6 (GPB5)
/O_GPB6: R79.1, U14.7 (GPB6)
/O_GPB7: R78.1, U14.8 (GPB7)
/PE: J18.1, J55.1, J56.1, J57.1, J58.1, J59.1, J60.1, J63.1, J64.1, J65.1, J66.1
/SPISCK: J19.4, J26.3, U14.12 (SCK), U35.4 (VIB)
/Ub_5V_RS485_BUS: C16.1, C84.1, J20.2, U11.6 (Out+)
/Ub_CAN_BUS: C17.1, C85.1, J21.1, U12.6 (Out+)
/~RESET: C98.2, J19.1, U14.18 (~RESET)
/~SPICS_DAC: J26.1, U35.3 (VIA)
/~SPICS_IO: J19.5, U14.11 (~CS)
GNDA: C27.1, C28.1, C29.2, C32.1, C33.1, C34.1, C36.2, C37.1, C38.1, C40.1, C44.1, C83.2, C88.2, C89.2, J31.1, J47.2, R69.2, R120.2, U35.9 (GND2), U35.11 (VID), U35.15 (GND2), U37.1 (GND), U38.12 (AVSS), U41.4 (V-), U44.4 (Out-), U45.4 (GND)
GNDD: C11.2, C12.2, C13.2, C14.2, C15.2, C18.1, C19.2, C26.1, C35.2, C39.2, C49.2, C80.2, C81.2, C82.2, C86.1, C87.1, C96.2, C97.2, C98.1, D51.2 (A2), J18.2, J19.6, J24.2, J26.4, J34.1, J53.1, U11.2 (In-), U12.2 (In-), U13.1 (GND), U14.10 (VSS), U14.16 (A1), U14.17 (A2), U15.2, U15.4, U15.6, U15.8, U16.2, U16.4, U16.6, U16.8, U17.2, U17.4, U17.6, U17.8, U18.2, U18.4, U18.6, U18.8, U35.2 (GND1), U35.7 (VE1), U35.8 (GND1), U44.2 (In-), U46.2 (GND), U51.3 (GNDD)
unnamed: C87.2, D48.2 (A), L1.1
unnamed: C36.1, C83.1, D53.2 (A), U44.6 (Out+)
unnamed: C88.1, D53.1 (K), L3.2
unnamed: D54.2 (A), U16.9
unnamed: D54.1 (K), R141.2, U26.3 (IN)
unnamed: D55.2 (A), U16.11
unnamed: D55.1 (K), R140.2, U25.3 (IN)
unnamed: D56.2 (A), U16.13
unnamed: D56.1 (K), R139.2, U24.3 (IN)
unnamed: D57.2 (A), U16.15
unnamed: D57.1 (K), R138.2, U23.3 (IN)
unnamed: D58.2 (A), U15.9
unnamed: D58.1 (K), R137.2, U22.3 (IN)
unnamed: D59.2 (A), U15.11
unnamed: D59.1 (K), R136.2, U21.3 (IN)
unnamed: D60.2 (A), U15.13
unnamed: D60.1 (K), R135.2, U20.3 (IN)
unnamed: D61.2 (A), U15.15
unnamed: D61.1 (K), R134.2, U19.3 (IN)
unnamed: D62.2 (A), U18.9
unnamed: D62.1 (K), R149.2, U34.3 (IN)
unnamed: D63.2 (A), U18.11
unnamed: D63.1 (K), R148.2, U33.3 (IN)
unnamed: D64.2 (A), U18.13
unnamed: D64.1 (K), R147.2, U32.3 (IN)
unnamed: D65.2 (A), U18.15
unnamed: D65.1 (K), R146.2, U31.3 (IN)
unnamed: D66.2 (A), U17.9
unnamed: D66.1 (K), R145.2, U30.3 (IN)
unnamed: D67.2 (A), U17.11
unnamed: D67.1 (K), R144.2, U29.3 (IN)
unnamed: D68.2 (A), U17.13
unnamed: D68.1 (K), R143.2, U28.3 (IN)
unnamed: D69.2 (A), U17.15
unnamed: D69.1 (K), R142.2, U27.3 (IN)
unnamed: D71.1 (A1), J23.3, J49.9, U19.1 (OUT)
unnamed: D72.1 (A1), J23.4, J49.7, U20.1 (OUT)
unnamed: D73.1 (A1), J23.5, J49.6, U21.1 (OUT)
unnamed: D74.1 (A1), J23.6, J49.5, U22.1 (OUT)
unnamed: D75.1 (A1), J23.7, J49.4, U23.1 (OUT)
unnamed: D76.1 (A1), J23.8, J49.3, U24.1 (OUT)
unnamed: D77.1 (A1), J23.9, J49.2, U25.1 (OUT)
unnamed: D78.1 (A1), J23.10, J49.1, U26.1 (OUT)
unnamed: D80.1 (A1), J22.3, J50.9, U27.1 (OUT)
unnamed: D81.1 (A1), J22.4, J50.7, U28.1 (OUT)
unnamed: D82.1 (A1), J22.5, J50.6, U29.1 (OUT)
unnamed: D83.1 (A1), J22.6, J50.5, U30.1 (OUT)
unnamed: D84.1 (A1), J22.7, J50.4, U31.1 (OUT)
unnamed: D85.1 (A1), J22.8, J50.3, U32.1 (OUT)
unnamed: D86.1 (A1), J22.9, J50.2, U33.1 (OUT)
unnamed: D87.1 (A1), J22.10, J50.1, U34.1 (OUT)
unnamed: C86.2, J18.3, L1.2
unnamed: F4.1, J22.2, J35.1, J50.8, J50.10, J50.11, J50.12, J50.13
unnamed: F5.1, J23.2, J32.1, J49.8, J49.10, J49.11, J49.12, J49.13
unnamed: Q2.1 (G), R170.1, U51.4
unnamed: R70.2, U15.1
unnamed: R71.2, U15.3
unnamed: R72.2, U15.5
unnamed: R73.2, U15.7
unnamed: R74.2, U16.1
unnamed: R75.2, U16.3
unnamed: R76.2, U16.5
unnamed: R77.2, U16.7
unnamed: R78.2, U17.1
unnamed: R79.2, U17.3
unnamed: R80.2, U17.5
unnamed: R81.2, U17.7
unnamed: R82.2, U18.1
unnamed: R83.2, U18.3
unnamed: R84.2, U18.5
unnamed: R85.2, U18.7
unnamed: R86.2, U15.16
unnamed: R87.2, U15.14
unnamed: R88.2, U15.12
unnamed: R89.2, U15.10
unnamed: R90.2, U16.16
unnamed: R91.2, U16.14
unnamed: R92.2, U16.12
unnamed: R93.2, U16.10
unnamed: R94.2, U17.16
unnamed: R95.2, U17.14
unnamed: R96.2, U17.12
unnamed: R97.2, U17.10
unnamed: R98.2, U18.16
unnamed: R99.2, U18.14
unnamed: R100.2, U18.12
unnamed: R101.2, U18.10
unnamed: C11.1, F3.1, U11.1 (In+)
unnamed: C12.1, F6.1, U12.1 (In+)
unnamed: R67.2, U14.15 (A0)
unnamed: R157.2, U14.14 (SO)
unnamed: R68.2, U35.10 (VE2)
unnamed: U35.14 (VOA), U38.3 (~CS), U38.8 (~LDAC)
unnamed: U35.13 (VOB), U38.4 (SCK)
unnamed: U35.12 (VOC), U38.5 (SDI)
unnamed: R69.1, R121.2, U41.2 (-)
unnamed: R120.1, R122.2, U41.6 (-)
unnamed: C35.1, C80.1, F2.1, U44.1 (In+)
unnamed: C13.1, C81.1, F7.1, U46.1 (IN)

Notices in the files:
myT40-Controller/V3_KiCad_PCB/myT41-C.kicad_pcb:
2026.05.15  V3.1 M10,  CC BY-NC-SA
myT40-EXT-116-XD1/KiCad_PCB/myT40_Ext_116-XD1.kicad_pcb:
CC BY-NC-SA 2023, C.Niesen, Koenigswinter, Germany
CC BY-NC-SA 2024,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
myT40-PLC/V5_KiCad_PCB/OP.kicad_pcb:
CC BY-NC-SA 2025
CC BY-NC-SA 2020-2026
myT40-PLC/V5_KiCad_PCB/UP.kicad_pcb:
CC BY-NC-SA 2020-2025
parts and their libraries:
Copyright 2016 Accelerated Designs. All rights reserved.
